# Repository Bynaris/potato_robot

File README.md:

# potato_robot
Modular Potato Powered Robot

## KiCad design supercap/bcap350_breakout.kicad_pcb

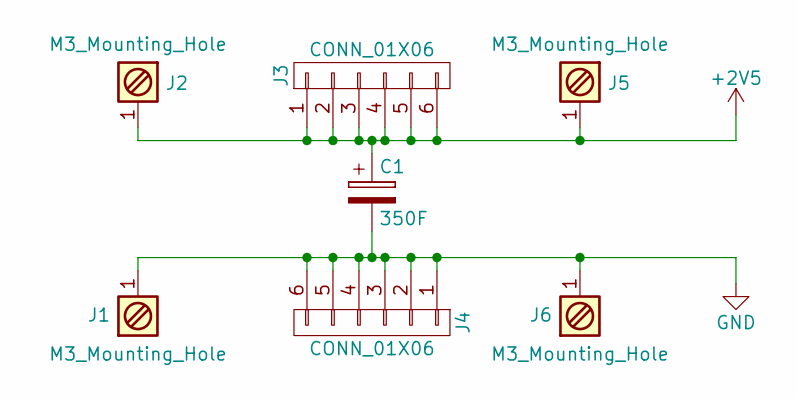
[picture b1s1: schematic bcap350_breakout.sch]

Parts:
C1: 350F; BCAP350
J1, J2, J5, J6: M3_Mounting_Hole; MountingHole_3.2mm_M3_Pad
J3, J4: CONN_01X06; Pin_Header_Straight_1x06_Pitch2.54mm

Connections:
+2V5: C1.1, J2.1, J3.1, J3.2, J3.3, J3.4, J3.5, J3.6, J5.1
GND: C1.2, J1.1, J4.1, J4.2, J4.3, J4.4, J4.5, J4.6, J6.1

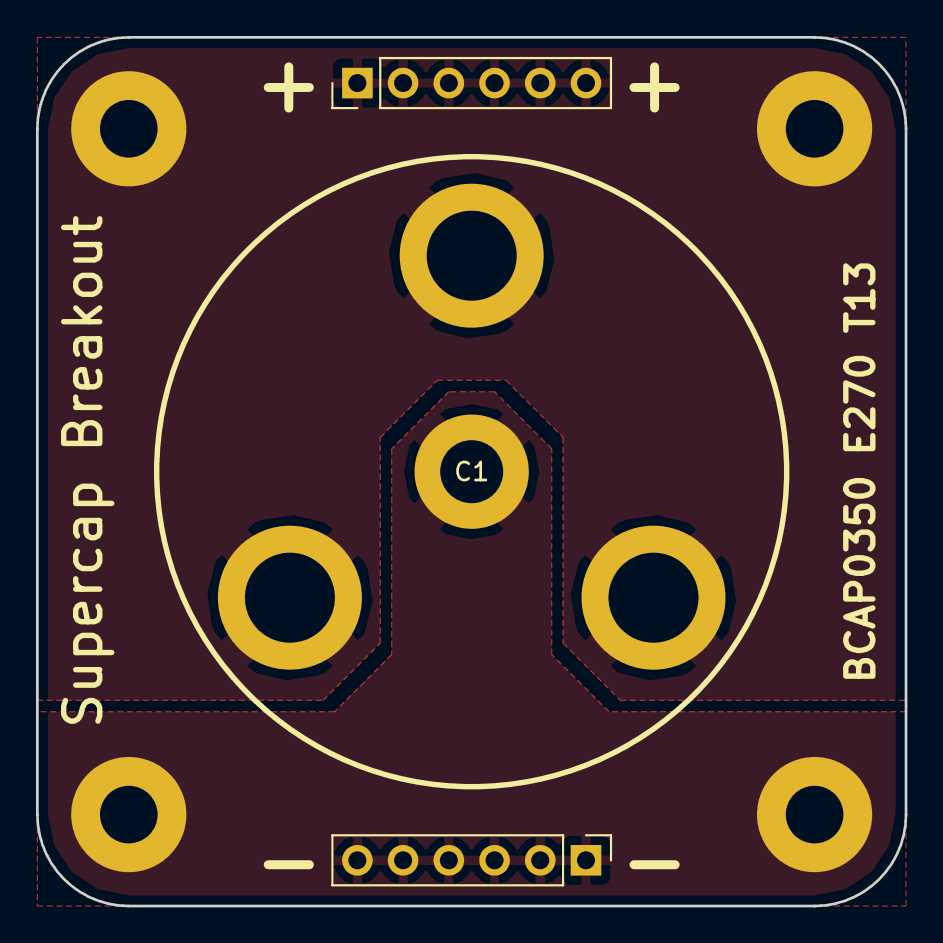
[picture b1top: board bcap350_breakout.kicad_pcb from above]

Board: 2 copper layers, 48.3 x 48.3 mm, 7 parts (0 on the bottom side), 2 nets.

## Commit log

2018-07-16 Add I2C_motor_driver files
